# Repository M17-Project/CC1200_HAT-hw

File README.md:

## CC1200_HAT-hw 
CC1200 RF Raspberry Pi Zero shield.

### Board overview

### Programming
See the [firmware's GitHub repository](https://github.com/M17-Project/CC1200_HAT-fw?tab=readme-ov-file#flashing)
for details.

### 40MHz TCXO
In case the `FT2MNTUM-40.0-T1` 40MHz crystal oscillator (X1) is not available, a valid replacement for it is `TG2520SMN 40.0000M-MCGNNM0`.

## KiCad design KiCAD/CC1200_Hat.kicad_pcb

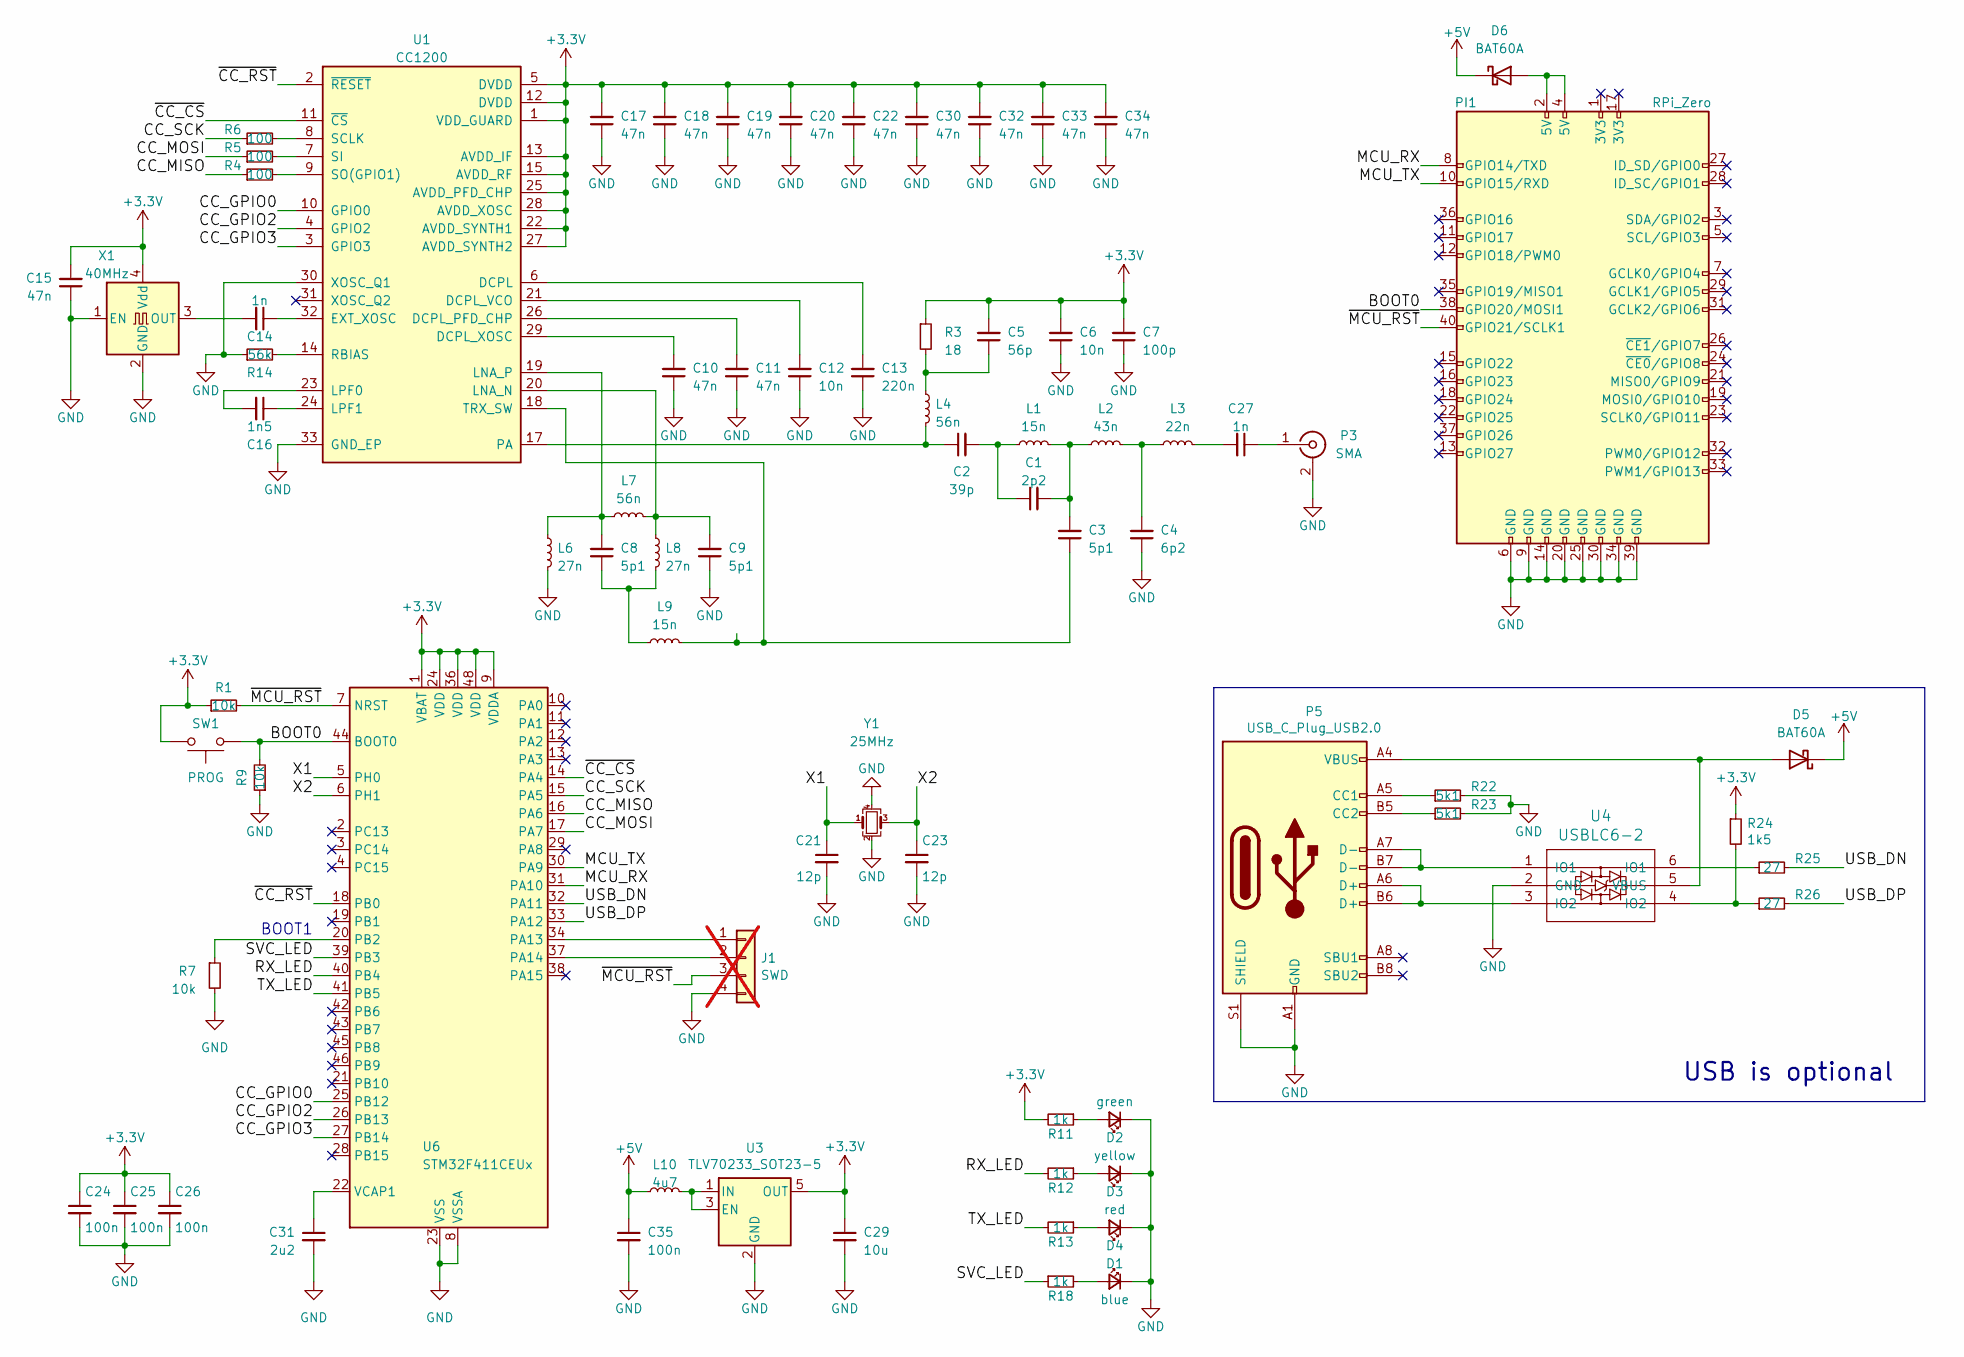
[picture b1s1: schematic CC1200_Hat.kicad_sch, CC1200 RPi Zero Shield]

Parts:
C1: 2p2; C_0402_1005Metric; MPN GCM1555C1H2R2BA16J
C2: 39p; C_0402_1005Metric; MPN GRM1555C2A390JA1D
C3, C8, C9: 5p1; C_0402_1005Metric; MPN GJM1555C1H5R1DB1D
C4: 6p2; C_0402_1005Metric; MPN GCM1555C1H6R2BA6D
C5: 56p; C_0402_1005Metric; MPN 04025A560JAT4A
C6, C12: 10n; C_0402_1005Metric; MPN 0402B103K6R3CT
C7: 100p; C_0402_1005Metric; MPN CL05C101JB5NNNC
C10, C11, C15, C17, C18, C19, C20, C22, C30, C32, C33, C34: 47n; C_0402_1005Metric; MPN GCM155L8EH473KE7D
C13: 220n; C_0402_1005Metric; MPN CGA2B3X5R1A224M050BB
C14, C27: 1n; C_0402_1005Metric; MPN GRT1555C1E102JA2J
C16: 1n5; C_0402_1005Metric; MPN 885012205026
C21, C23: 12p; C_0402_1005Metric; MPN C0402C120J5GACTU
C24, C25, C26, C35: 100n; C_0402_1005Metric; MPN VJ0402V104ZXJCW1BC
C29: 10u; C_0603_1608Metric; MPN CL10A106KQ8NNNC
C31: 2u2; C_0603_1608Metric; MPN CL10A225KO8NNWC
D1: blue; LED_0402_1005Metric; MPN APHHS1005QBC/D
D2: green; LED_0402_1005Metric; MPN APHHS1005CGCK
D3: yellow; LED_0402_1005Metric; MPN APG1005SYC-T
D4: red; LED_0402_1005Metric; MPN APHHS1005SURCK
D5, D6: BAT60A; D_SOD-323; MPN BAT60AE6327XT
J1: SWD; PinHeader_1x04_P2.54mm_Vertical; not fitted
L1, L9: 15n; L_0402_1005Metric; MPN LQG15HZ15NJ02D
L2: 43n; L_0402_1005Metric; MPN LQG15WZ43NJ02D
L3: 22n; L_0402_1005Metric; MPN LQG15HZ22NH02D
L4, L7: 56n; L_0402_1005Metric; MPN LCCI0402J56NGTAR
L6, L8: 27n; L_0402_1005Metric; MPN LQG15HN27NJ02D
L10: 4u7; L_0402_1005Metric; MPN PLEA67BCA4R7M-1PT00
P3: SMA; SMA_Wurth_60312002114503_Vertical; MPN RF2-04A-T-00-50-G
P5: USB_C_Plug_USB2.0; USB_C_Receptacle_HRO_TYPE-C-31-M-12; MPN TYPE-C-31-M-12
PI1: RPi_Zero; Raspberry_Pi_Zero_Socketed_THT_FaceDown_MountingHoles
R1, R7, R9: 10k; R_0402_1005Metric; MPN RC0402JR-1010KL
R3: 18; R_0402_1005Metric; MPN ERJ-2GEJ180X
R4, R5, R6: 100; R_0402_1005Metric; MPN CR0402AJW-101GLF
R11, R12, R13, R18: 1k; R_0402_1005Metric; MPN ERJ-PA2D1001X
R14: 56k; R_0402_1005Metric; MPN RK73B1ETTP563J
R22, R23: 5k1; R_0402_1005Metric; MPN RC0402FR-075K1L
R24: 1k5; R_0402_1005Metric; MPN AC0402JR-7W1K5L
R25, R26: 27; R_0402_1005Metric; MPN CRCW040210K0FKED
SW1: PROG; SW_Tactile_SPST_NO_Straight_CK_PTS636Sx25SMTRLFS; MPN PTS636SM43JSMTR LFS
U1: CC1200; QFN-32-1EP_5x5mm_P0.5mm_EP3.45x3.45mm; MPN CC1200RHBR
U3: TLV70233_SOT23-5; SOT-23-5; MPN TLV70233PDBVR
U4: USBLC6-2; SOT-23-6; MPN USBLC6-2SC6
U6: STM32F411CEUx; QFN-48-1EP_7x7mm_P0.5mm_EP5.6x5.6mm; MPN STM32F411CEU6
X1: 40MHz; Oscillator_SMD_SeikoEpson_SG210-4Pin_2.5x2.0mm; MPN FT2MNTUM-40.0-T1
Y1: 25MHz; Crystal_SMD_3225-4Pin_3.2x2.5mm; MPN EB2532YA08-25.000M TR

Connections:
+3.3V: C5.2, C6.2, C7.2, C15.2, C17.2, C18.2, C19.2, C20.2, C22.2, C24.1, C25.1, C26.1, C29.1, C30.2, C32.2, C33.2, C34.2, R1.1, R3.1, R11.2, R24.1, SW1.2, U1.1 (VDD_GUARD), U1.5 (DVDD), U1.12 (DVDD), U1.13 (AVDD_IF), U1.15 (AVDD_RF), U1.22 (AVDD_SYNTH1), U1.25 (AVDD_PFD_CHP), U1.27 (AVDD_SYNTH2), U1.28 (AVDD_XOSC), U3.5 (OUT), U6.1 (VBAT), U6.9 (VDDA), U6.24 (VDD), U6.36 (VDD), U6.48 (VDD), X1.4 (Vdd)
+5V: C35.1, D5.1 (K), D6.1 (K), L10.1
/BOOT0: PI1.38 (GPIO20/MOSI1), R9.2, SW1.1, U6.44 (BOOT0)
/CC_GPIO0: U1.10 (GPIO0), U6.25 (PB12)
/CC_GPIO2: U1.4 (GPIO2), U6.26 (PB13)
/CC_GPIO3: U1.3 (GPIO3), U6.27 (PB14)
/CC_MISO: R4.1, U6.16 (PA6)
/CC_MOSI: R5.1, U6.17 (PA7)
/CC_SCK: R6.1, U6.15 (PA5)
/MCU_RX: PI1.8 (GPIO14/TXD), U6.31 (PA10)
/MCU_TX: PI1.10 (GPIO15/RXD), U6.30 (PA9)
/RX_LED: R12.2, U6.40 (PB4)
/SVC_LED: R18.1, U6.39 (PB3)
/TX_LED: R13.2, U6.41 (PB5)
/USB_DN: R25.2, U6.32 (PA11)
/USB_DP: R26.2, U6.33 (PA12)
/X1: C21.1, U6.5 (PH0), Y1.1
/X2: C23.1, U6.6 (PH1), Y1.3
/~CC_CS: U1.11 (~CS), U6.14 (PA4)
/~CC_RST: U1.2 (~RESET), U6.18 (PB0)
/~MCU_RST: J1.3, PI1.40 (GPIO21/SCLK1), R1.2, U6.7 (NRST)
GND: C4.1, C6.1, C7.1, C9.1, C10.1, C11.1, C12.1, C13.1, C15.1, C17.1, C18.1, C19.1, C20.1, C21.2, C22.1, C23.2, C24.2, C25.2, C26.2, C29.2, C30.1, C31.2, C32.1, C33.1, C34.1, C35.2, D1.1 (K), D2.1 (K), D3.1 (K), D4.1 (K), J1.4, L6.2, P3.2 (Ext), P5.A1 (GND), P5.A12 (GND), P5.B1 (GND), P5.B12 (GND), P5.S1 (SHIELD), PI1.6 (GND), PI1.9 (GND), PI1.14 (GND), PI1.20 (GND), PI1.25 (GND), PI1.30 (GND), PI1.34 (GND), PI1.39 (GND), R7.2, R9.1, R14.1, R22.2, R23.2, U1.30 (XOSC_Q1), U1.33 (GND_EP), U3.2 (GND), U4.2 (GND), U6.8 (VSSA), U6.23 (VSS), U6.35 (VSS), U6.47 (VSS), U6.49 (VSS), X1.1 (EN), X1.2 (GND), Y1.2, Y1.4
unnamed: C1.1, C2.2, L1.1
unnamed: C1.2, C3.2, L1.2, L2.1
unnamed: C4.2, L2.2, L3.1
unnamed: C5.1, L4.1, R3.2
unnamed: C8.1, L8.2, L9.1
unnamed: C27.2, L3.2
unnamed: D1.2 (A), R18.2
unnamed: D2.2 (A), R11.1
unnamed: D3.2 (A), R12.1
unnamed: D4.2 (A), R13.1
unnamed: D5.2 (A), P5.A4 (VBUS), P5.A9 (VBUS), P5.B4 (VBUS), P5.B9 (VBUS), U4.5 (VBUS)
unnamed: D6.2 (A), PI1.2 (5V), PI1.4 (5V)
unnamed: J1.1, U6.34 (PA13)
unnamed: J1.2, U6.37 (PA14)
unnamed: C27.1, P3.1 (In)
unnamed: P5.A5 (CC1), R22.1
unnamed: P5.B5 (CC2), R23.1
unnamed: P5.A6 (D+), P5.B6 (D+), U4.3 (IO2)
unnamed: P5.A7 (D-), P5.B7 (D-), U4.1 (IO1)
unnamed: R24.2, R26.1, U4.4 (IO2)
unnamed: R25.1, U4.6 (IO1)
unnamed: C13.2, U1.6 (DCPL)
unnamed: C11.2, U1.26 (DCPL_PFD_CHP)
unnamed: C12.2, U1.21 (DCPL_VCO)
unnamed: C10.2, U1.29 (DCPL_XOSC)
unnamed: C14.1, U1.32 (EXT_XOSC)
unnamed: C9.2, L7.2, L8.1, U1.20 (LNA_N)
unnamed: C8.2, L6.1, L7.1, U1.19 (LNA_P)
unnamed: C16.2, U1.23 (LPF0)
unnamed: C16.1, U1.24 (LPF1)
unnamed: C2.1, L4.2, U1.17 (PA)
unnamed: R14.2, U1.14 (RBIAS)
unnamed: R6.2, U1.8 (SCLK)
unnamed: R5.2, U1.7 (SI)
unnamed: R4.2, U1.9 (SO(GPIO1))
unnamed: C3.1, L9.2, U1.18 (TRX_SW)
unnamed: L10.2, U3.1 (IN), U3.3 (EN)
unnamed: R7.1, U6.20 (PB2)
unnamed: C31.1, U6.22 (VCAP1)
unnamed: C14.2, X1.3 (OUT)

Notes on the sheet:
BOOT1
USB is optional

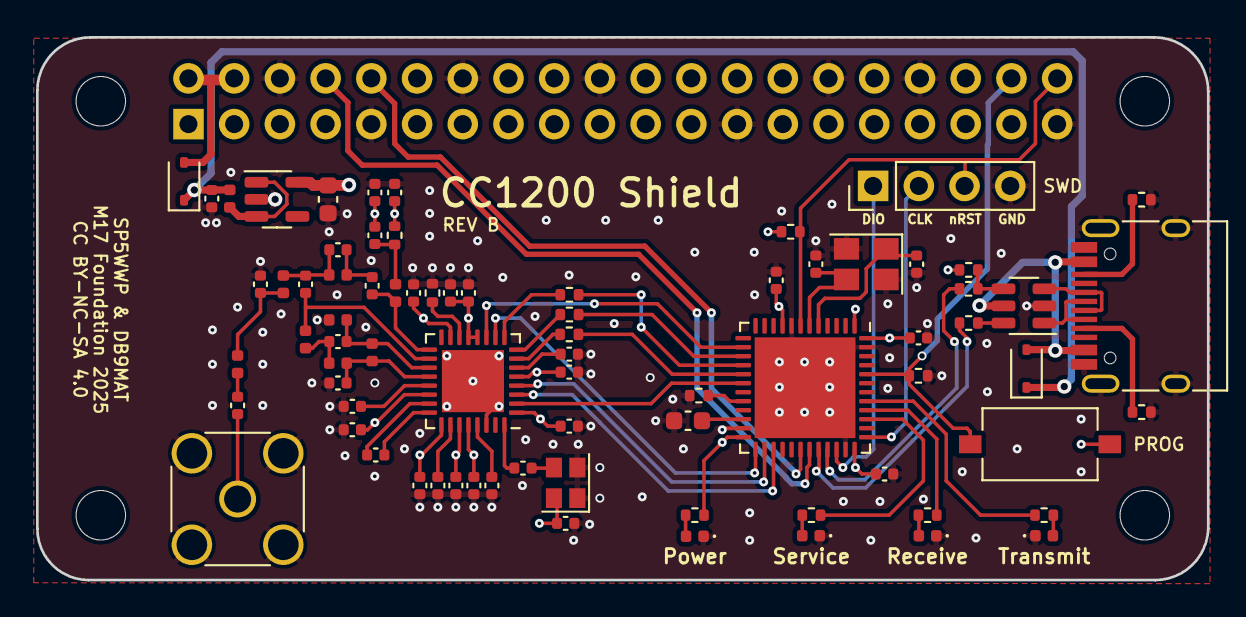
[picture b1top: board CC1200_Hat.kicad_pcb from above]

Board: 4 copper layers, 65.1 x 30.2 mm, 77 parts (1 on the bottom side), 62 nets.

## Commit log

2024-10-21 added license
2025-02-06 cleanup/update
    - schematic/pcb cleanup
    - WIP PN assignment
    - KiCAD version update
2025-02-07 minor updates
    - pcb update - "PROG" button
    - readme update
    - WIP PN update
2025-02-07 PN assignment
2025-02-10 MPN fixes for Mouser
2025-03-10 updates
    - KiCAD version bump to 9.0
    - BOM value update for R25 & R26
2025-05-26 Update README.md
    programming over USB works
2025-05-28 Update README.md
    40MHz TCXO info
2025-05-28 Update README.md
    hopefully this X1 TCXO replacement is fine

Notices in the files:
KiCAD/CC1200_Hat.kicad_pcb:
CC BY-NC-SA 4.0
